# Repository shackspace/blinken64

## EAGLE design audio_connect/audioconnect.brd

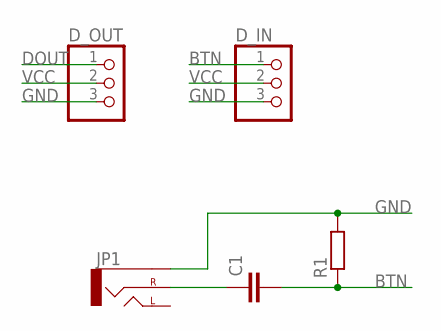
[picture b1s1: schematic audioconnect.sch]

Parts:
C1: C-EUC1206; C1206
D_IN: PINHD-1X03_2.54-S; 1X03-S
D_OUT: PINHD-1X03_2.54-S; 1X03-S
JP1: AUDIO-JACKPTH; AUDIO-JACK
R1: R-EU_R1206; R1206

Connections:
BTN: C1.2, D_IN.1, R1.1
DOUT: D_OUT.1
GND: D_IN.3, D_OUT.3, JP1.SLEEVE, R1.2
unnamed: C1.1, JP1.RING (RIGHT)
VCC: D_IN.2, D_OUT.2

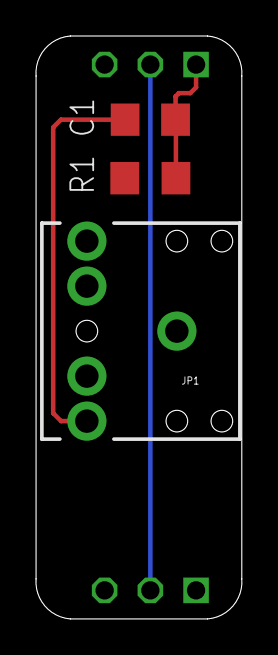
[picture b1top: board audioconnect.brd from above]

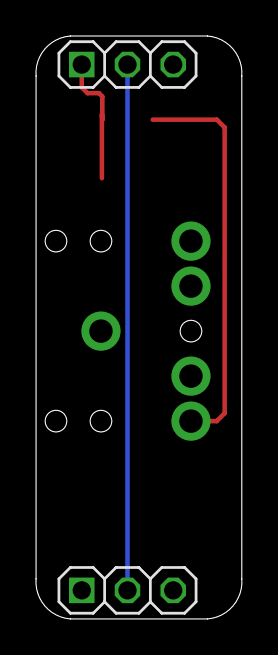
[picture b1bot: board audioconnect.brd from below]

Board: 2 copper layers, 11.4 x 32.4 mm, 5 parts (2 on the bottom side), 4 nets.

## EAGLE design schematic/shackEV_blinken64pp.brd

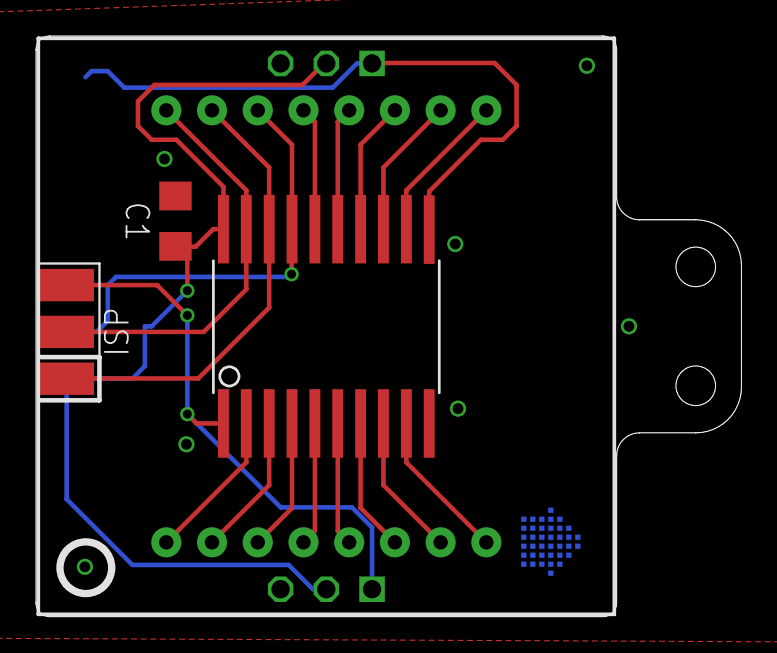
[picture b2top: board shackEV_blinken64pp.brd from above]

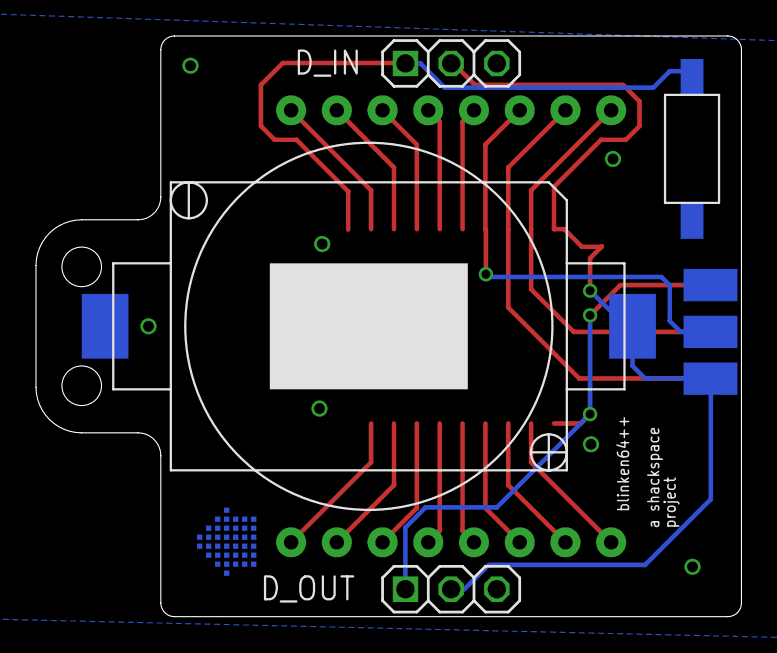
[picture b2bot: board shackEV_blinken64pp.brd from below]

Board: 2 copper layers, 39.2 x 32.3 mm, 8 parts (4 on the bottom side), 20 nets.

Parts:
BATTERY_1: 2032; KZH20SMD
C1: C1206
D_IN: 1X03-S
D_OUT: 1X03-S
ISP1: SMD-ISP; SMD
LED2: MICROBUILDER_SEGMENT_BL-M12A881UR
SW1: SWITCH-2PSWITCH-GENERAL-2P; 2P-SWITCH-GENERAL
U$2: TINY2313-*S*; SO20L$

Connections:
1: LED2.1, U$2.2
2: LED2.2, U$2.3
3: LED2.3, U$2.4
4: LED2.4, U$2.5
5: LED2.5, U$2.6
6: LED2.6, U$2.7
7: LED2.7, U$2.8
8: LED2.8, U$2.9
9: LED2.9, U$2.12
10: LED2.10, U$2.13
11: LED2.11, U$2.14
12: LED2.12, U$2.15
13: LED2.13, U$2.16
14: ISP1.MOSI, LED2.14, U$2.17
15: ISP1.MISO, LED2.15, U$2.18
16: ISP1.SCK, LED2.16, U$2.19
BTN: D_IN.1, SW1.P$2, U$2.11
DOUT: D_OUT.1, ISP1.RESET, U$2.1
GND: BATTERY_1.-, C1.2, D_IN.3, D_OUT.3, ISP1.GND, SW1.P$1, U$2.10
VCC: BATTERY_1.+, C1.1, D_IN.2, D_OUT.2, ISP1.VCC, U$2.20

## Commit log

2014-11-26 This commit add the files from http://nomnom.de/projects/blinken64/blinken64.zip This is the first blinken64V1 version more information: http://shackspace.de/wiki/doku.php?id=project:blinken64v1
2014-11-26 Add new branch with current version
2014-11-28 move microcontroller code into subfolder firmware
2014-11-28 remove/change path
2014-11-28 makefile: compile external tools
2014-11-28 .gitignore rm *.lss *.bin tools/executables
2014-11-28 bypass external.sh
2014-11-29 makefile: implement workflow dependencies
2014-11-29 Add shacklogo

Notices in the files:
parts and their libraries:
SparkFun-Connectors: Licensing: Creative Commons ShareAlike 4.0 International - https://creativecommons.org/licenses/by-sa/4.0
